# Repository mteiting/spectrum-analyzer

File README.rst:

..  Copyright 2014-present PlatformIO <contact@platformio.org>
    Licensed under the Apache License, Version 2.0 (the "License");
    you may not use this file except in compliance with the License.
    You may obtain a copy of the License at
       http://www.apache.org/licenses/LICENSE-2.0
    Unless required by applicable law or agreed to in writing, software
    distributed under the License is distributed on an "AS IS" BASIS,
    WITHOUT WARRANTIES OR CONDITIONS OF ANY KIND, either express or implied.
    See the License for the specific language governing permissions and
    limitations under the License.

How to build PlatformIO based project
=====================================

1. `Install PlatformIO Core <http://docs.platformio.org/page/core.html>`_
2. Download `development platform with examples <https://github.com/platformio/platform-espressif8266/archive/develop.zip>`_
3. Extract ZIP archive
4. Run these commands:

.. code-block:: bash

    # Change directory to example
    > cd platform-espressif8266/examples/arduino-webserver

    # Build project
    > platformio run

    # Upload firmware
    > platformio run --target upload

    # Build specific environment
    > platformio run -e nodemcuv2

    # Upload firmware for the specific environment
    > platformio run -e nodemcuv2 --target upload

    # Clean build files
    > platformio run --target clean

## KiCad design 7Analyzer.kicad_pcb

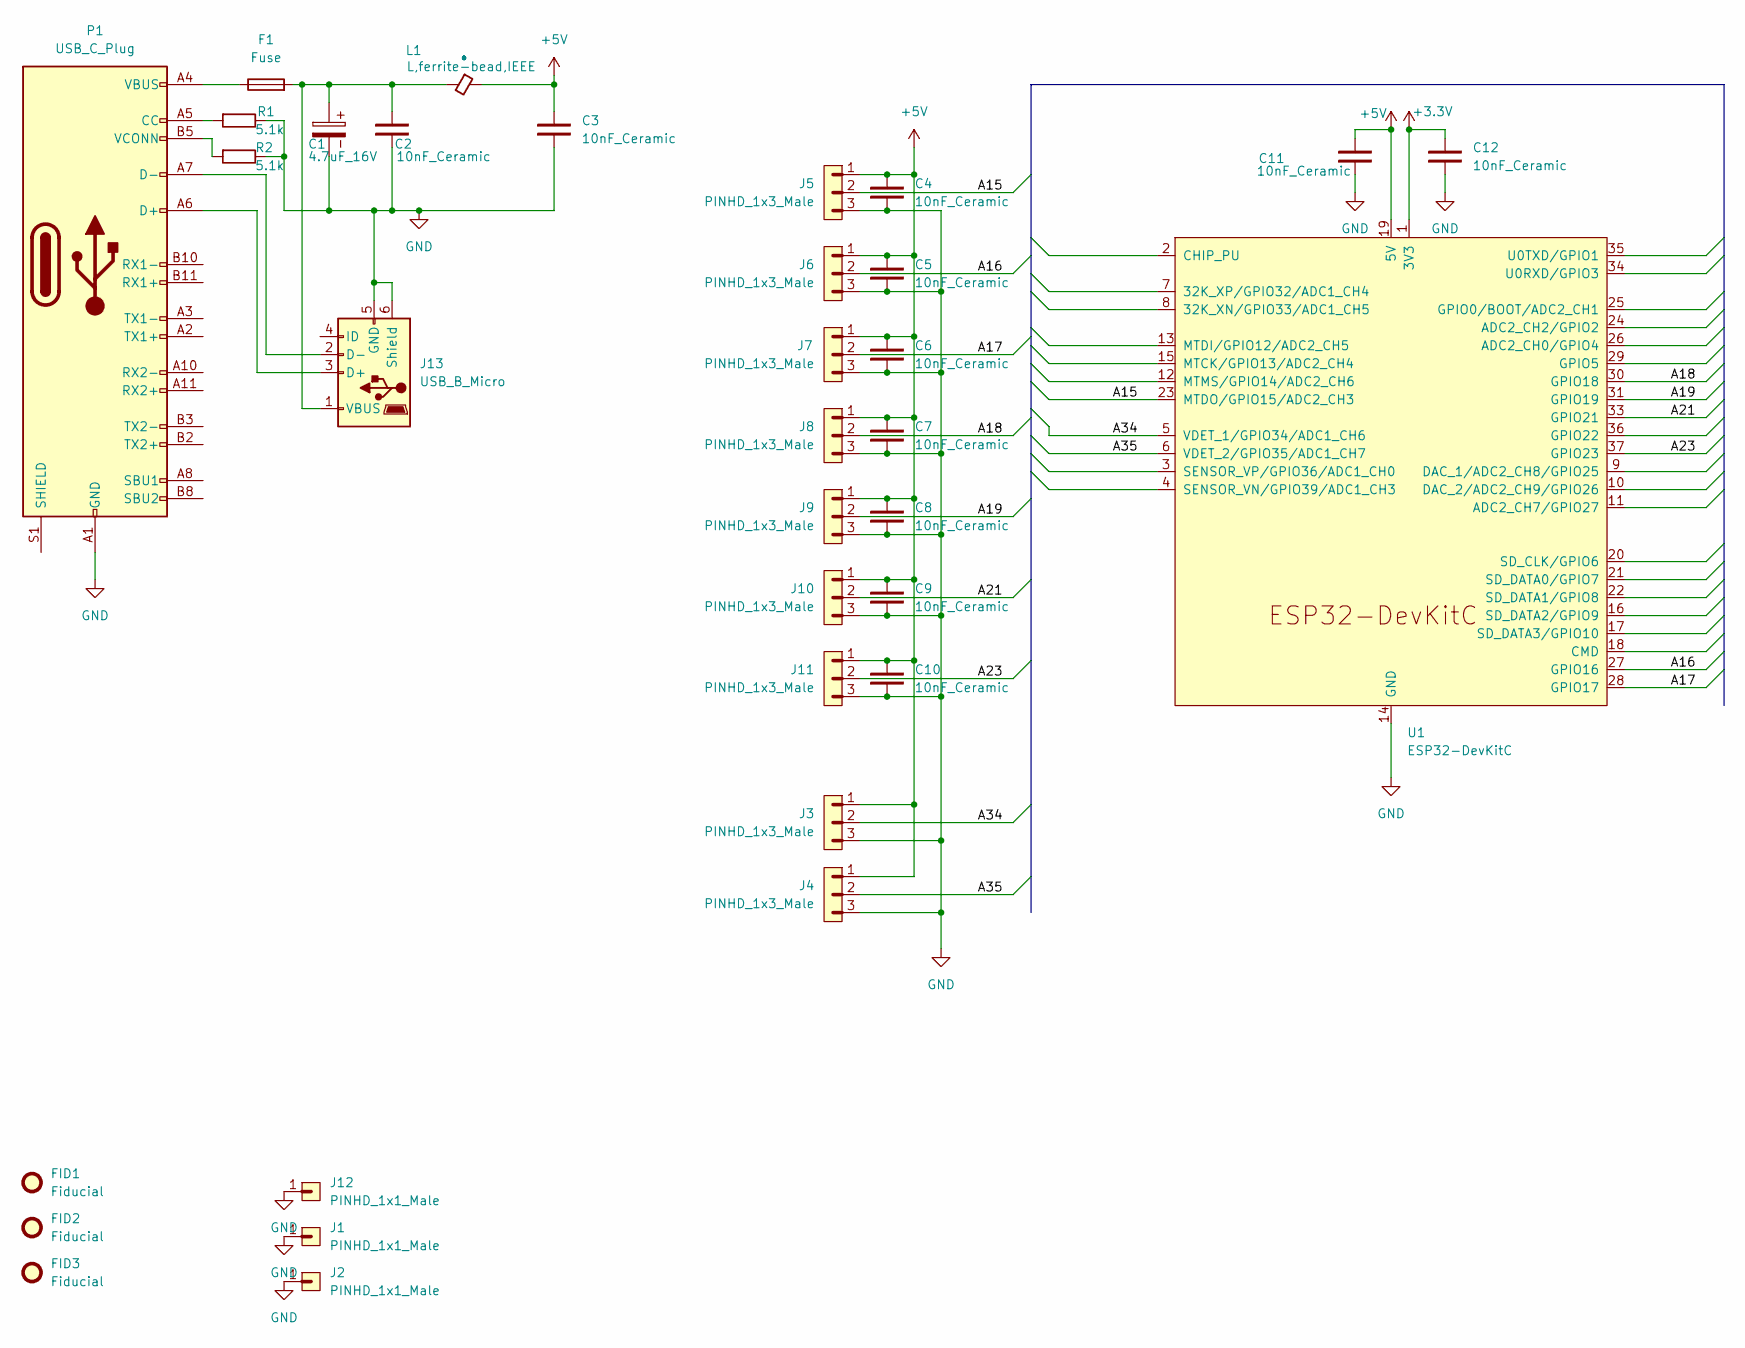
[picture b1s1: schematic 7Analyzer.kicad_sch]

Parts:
C1: 4.7uF_16V; CP_Radial_D5.0mm_P2.00mm
C2, C3, C4, C5, C6, C7, C8, C9, C10, C11, C12: 10nF_Ceramic; LED_0805_2012Metric_Pad1.15x1.40mm_HandSolder
F1: Fuse; Fuse_1210_3225Metric_Pad1.42x2.65mm_HandSolder
FID1, FID2, FID3: Fiducial; Fiducial_0.75mm_Mask2.25mm
J1, J2, J12: PINHD_1x1_Male; MountingHole_3.5mm_Pad
J3, J4, J5, J6, J7, J8, J9, J10, J11: PINHD_1x3_Male; PinHeader_1x03_P2.54mm_Vertical
J13: USB_B_Micro; USB_Micro-B_Amphenol_10118193-0002LF_Horizontal
L1: L,ferrite-bead,IEEE; LED_0805_2012Metric_Pad1.15x1.40mm_HandSolder
P1: USB_C_Plug; USB_C_Receptacle_GCT_USB4105-xx-A_16P_TopMnt_Horizontal
R1, R2: 5.1k; R_0805_2012Metric_Pad1.20x1.40mm_HandSolder
U1: ESP32-DevKitC

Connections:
+3.3V: C12.2, U1.1 (3V3)
+5V: C3.2, C4.2, C5.2, C6.2, C7.2, C8.2, C9.2, C10.2, C11.2, J3.1, J4.1, J5.1, J6.1, J7.1, J8.1, J9.1, J10.1, J11.1, L1.1 (+), U1.19 (5V)
/A15: J5.2, U1.23 (MTDO/GPIO15/ADC2_CH3)
/A16: J6.2, U1.27 (GPIO16)
/A17: J7.2, U1.28 (GPIO17)
/A18: J8.2, U1.30 (GPIO18)
/A19: J9.2, U1.31 (GPIO19)
/A21: J10.2, U1.33 (GPIO21)
/A23: J11.2, U1.37 (GPIO23)
/A34: J3.2, U1.5 (VDET_1/GPIO34/ADC1_CH6)
/A35: J4.2, U1.6 (VDET_2/GPIO35/ADC1_CH7)
GND: C1.2, C2.1, C3.1, C4.1, C5.1, C6.1, C7.1, C8.1, C9.1, C10.1, C11.1, C12.1, J1.1, J2.1, J3.3, J4.3, J5.3, J6.3, J7.3, J8.3, J9.3, J10.3, J11.3, J12.1, J13.5 (GND), J13.6 (Shield), P1.A1 (GND), P1.A12 (GND), P1.B1 (GND), P1.B12 (GND), R1.2, R2.2, U1.14 (GND), U1.32 (GND), U1.38 (GND)
unnamed: F1.1, P1.A4 (VBUS), P1.A9 (VBUS), P1.B4 (VBUS), P1.B9 (VBUS)
unnamed: J13.3 (D+), P1.A6 (D+)
unnamed: J13.2 (D-), P1.A7 (D-)
unnamed: C1.1, C2.2, F1.2, J13.1 (VBUS), L1.2 (-)
unnamed: P1.A5 (CC), R1.1
unnamed: P1.B5 (VCONN), R2.1

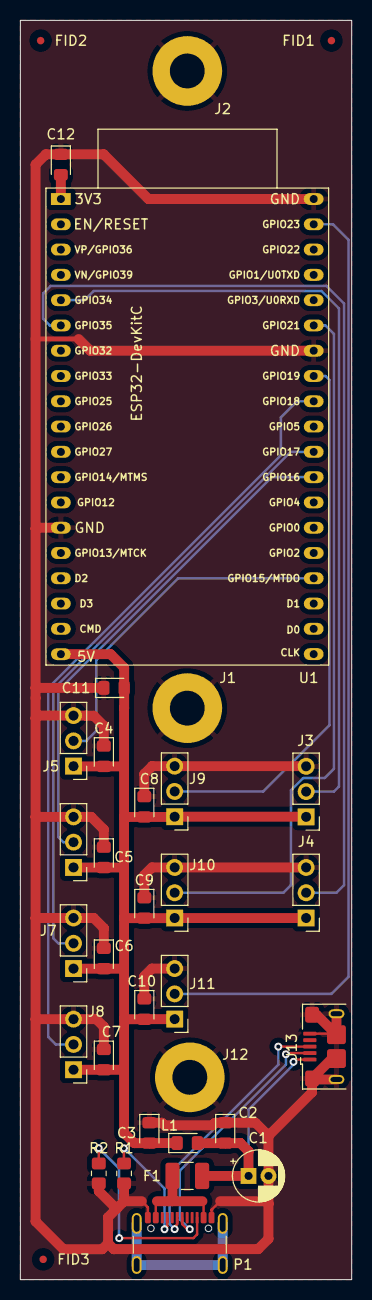
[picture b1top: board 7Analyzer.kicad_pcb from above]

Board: 2 copper layers, 33.3 x 126.5 mm, 34 parts (0 on the bottom side), 18 nets.

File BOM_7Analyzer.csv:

"Id";"Designator";"Footprint";"Quantity";"Designation";"Supplier and ref";
1;"J10,J9,J8,J5,J3,J11,J6,J7,J4";"PinHeader_1x03_P2.54mm_Vertical";9;"PINHD_1x3_Male";;;
2;"J2,J1,J12";"MountingHole_3.5mm_Pad";3;"PINHD_1x1_Male";;;
3;"U1";"ESP32-DevKitC";1;"ESP32-DevKitC";;;
4;"C11,C2,C7,C12,C8,C9,C6,C3,C5,C10,C4";"LED_0805_2012Metric_Pad1.15x1.40mm_HandSolder";11;"10nF_Ceramic";;;
5;"R2,R1";"R_0805_2012Metric_Pad1.20x1.40mm_HandSolder";2;"5.1k";;;
6;"C1";"CP_Radial_D5.0mm_P2.00mm";1;"4.7uF_16V";;;
7;"F1";"Fuse_1210_3225Metric_Pad1.42x2.65mm_HandSolder";1;"Fuse";;;
8;"L1";"LED_0805_2012Metric_Pad1.15x1.40mm_HandSolder";1;"L,ferrite-bead,IEEE";;;
9;"J13";"USB_Micro-B_Amphenol_10118193-0002LF_Horizontal";1;"USB_B_Micro";;;
10;"P1";"USB_C_Receptacle_GCT_USB4105-xx-A_16P_TopMnt_Horizontal";1;"USB_C_Plug";;;

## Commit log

2021-07-15 init 🎉
2021-07-22 Wifi
    Wifi start
2021-10-28 Arduino
    Arduino
2021-10-28 SSID mit MAC sowie warten auf SerialInterface
2021-10-28 html
2022-07-18 switch to esp32
2022-07-18 Wifi AccessPoint
2022-07-18 WS2812 includiert
2022-07-19 kaputt
2022-07-19 jetzt tuts wieder
2022-07-19 4 band test
2022-07-19 led an 100 angepasst
2022-07-19 wifi ausgelagert
2022-07-19 jetzt
2022-07-19 ka was
2022-07-19 new functions for level and color
2022-07-19 test tut für random level bei 5 baendern
2022-07-19 fft oder signal... kp
2022-07-19 fix i2c frequency
2022-07-20 mic rausgeschmissen
2022-07-20 level und delay für peak led eingebaut
2022-07-20 code optimiert
2022-07-20 timer ausgelagert
2022-07-20 zeit angepasst
2022-07-20 Name angepasst
2022-07-21 lib hinzugefügt, sowie html seite in der header erstellt
2022-07-21 scan button
2022-07-21 scanning und select in html drinne
2022-07-21 button entfernt
2022-07-21 erste Version von der html page
2022-07-21 delay in band berechnet
2022-07-21 push
2022-07-21 fehler beim peakledtimer
2022-07-22 fft gedoense ausgelagert
2022-07-22 sdafsf
2022-07-22 peak delay timer nun pro band klasse
2022-07-22 hinteren Frequenzbänder verstärkt
2022-07-24 println entfernt
2022-08-04 shared_ptr eingebaut, weils geht und Marcel doof ist :D
2023-07-17 format
2023-07-17 seperate strip from analyzer and add this to the band
2023-07-18 add defaults, add inline functions
2023-07-19 add simluation and led test
2023-07-20 add new constructor and define pins for first version
2023-07-20 add Filehandling
2023-07-20 add Stationmode
2023-07-20 frontend/webserver and wifi bugfixes
2023-07-21 added toggle all & fading and color customization
2023-09-21 adding github actions
2023-09-21 fix artifacts
2023-09-21 adding da
2023-09-21 adding timestamp
2023-09-21 using environment file
2023-09-21 debugging build date
2023-09-21 fixing build_date
2023-09-21 too late
2023-09-21 adding release builds
2023-09-21 fix file upload on release
2023-09-21 testing version
2023-09-21 found error
2023-09-21 get latest tag
2023-09-21 testing version increment
2023-09-21 debugging
2023-09-21 versioning...
2023-09-21 some changes
2024-07-29 version1.0
2024-07-30 laengere Version
2024-07-31 add micro usb to connect esp32
2024-08-01 add gitignore
2024-08-01 change for i2s error
2025-06-05 ich hab keine Ahnung
2025-06-12 create gerber files for v2
2025-07-22 add double adc on CH6&7 with raw ADC. Disable I2C for future mics
2025-07-22 Verbessere ADC-Implementierung für Kanäle 6 und 7 mit maximaler Abtastung; aktualisiere Kommentare zur Klarheit
2025-07-22 Entferne kommentierte Pin-Nummern in led.h für bessere Lesbarkeit
2025-07-24 new bom and current HW version
2025-09-12 add morse code simulation
